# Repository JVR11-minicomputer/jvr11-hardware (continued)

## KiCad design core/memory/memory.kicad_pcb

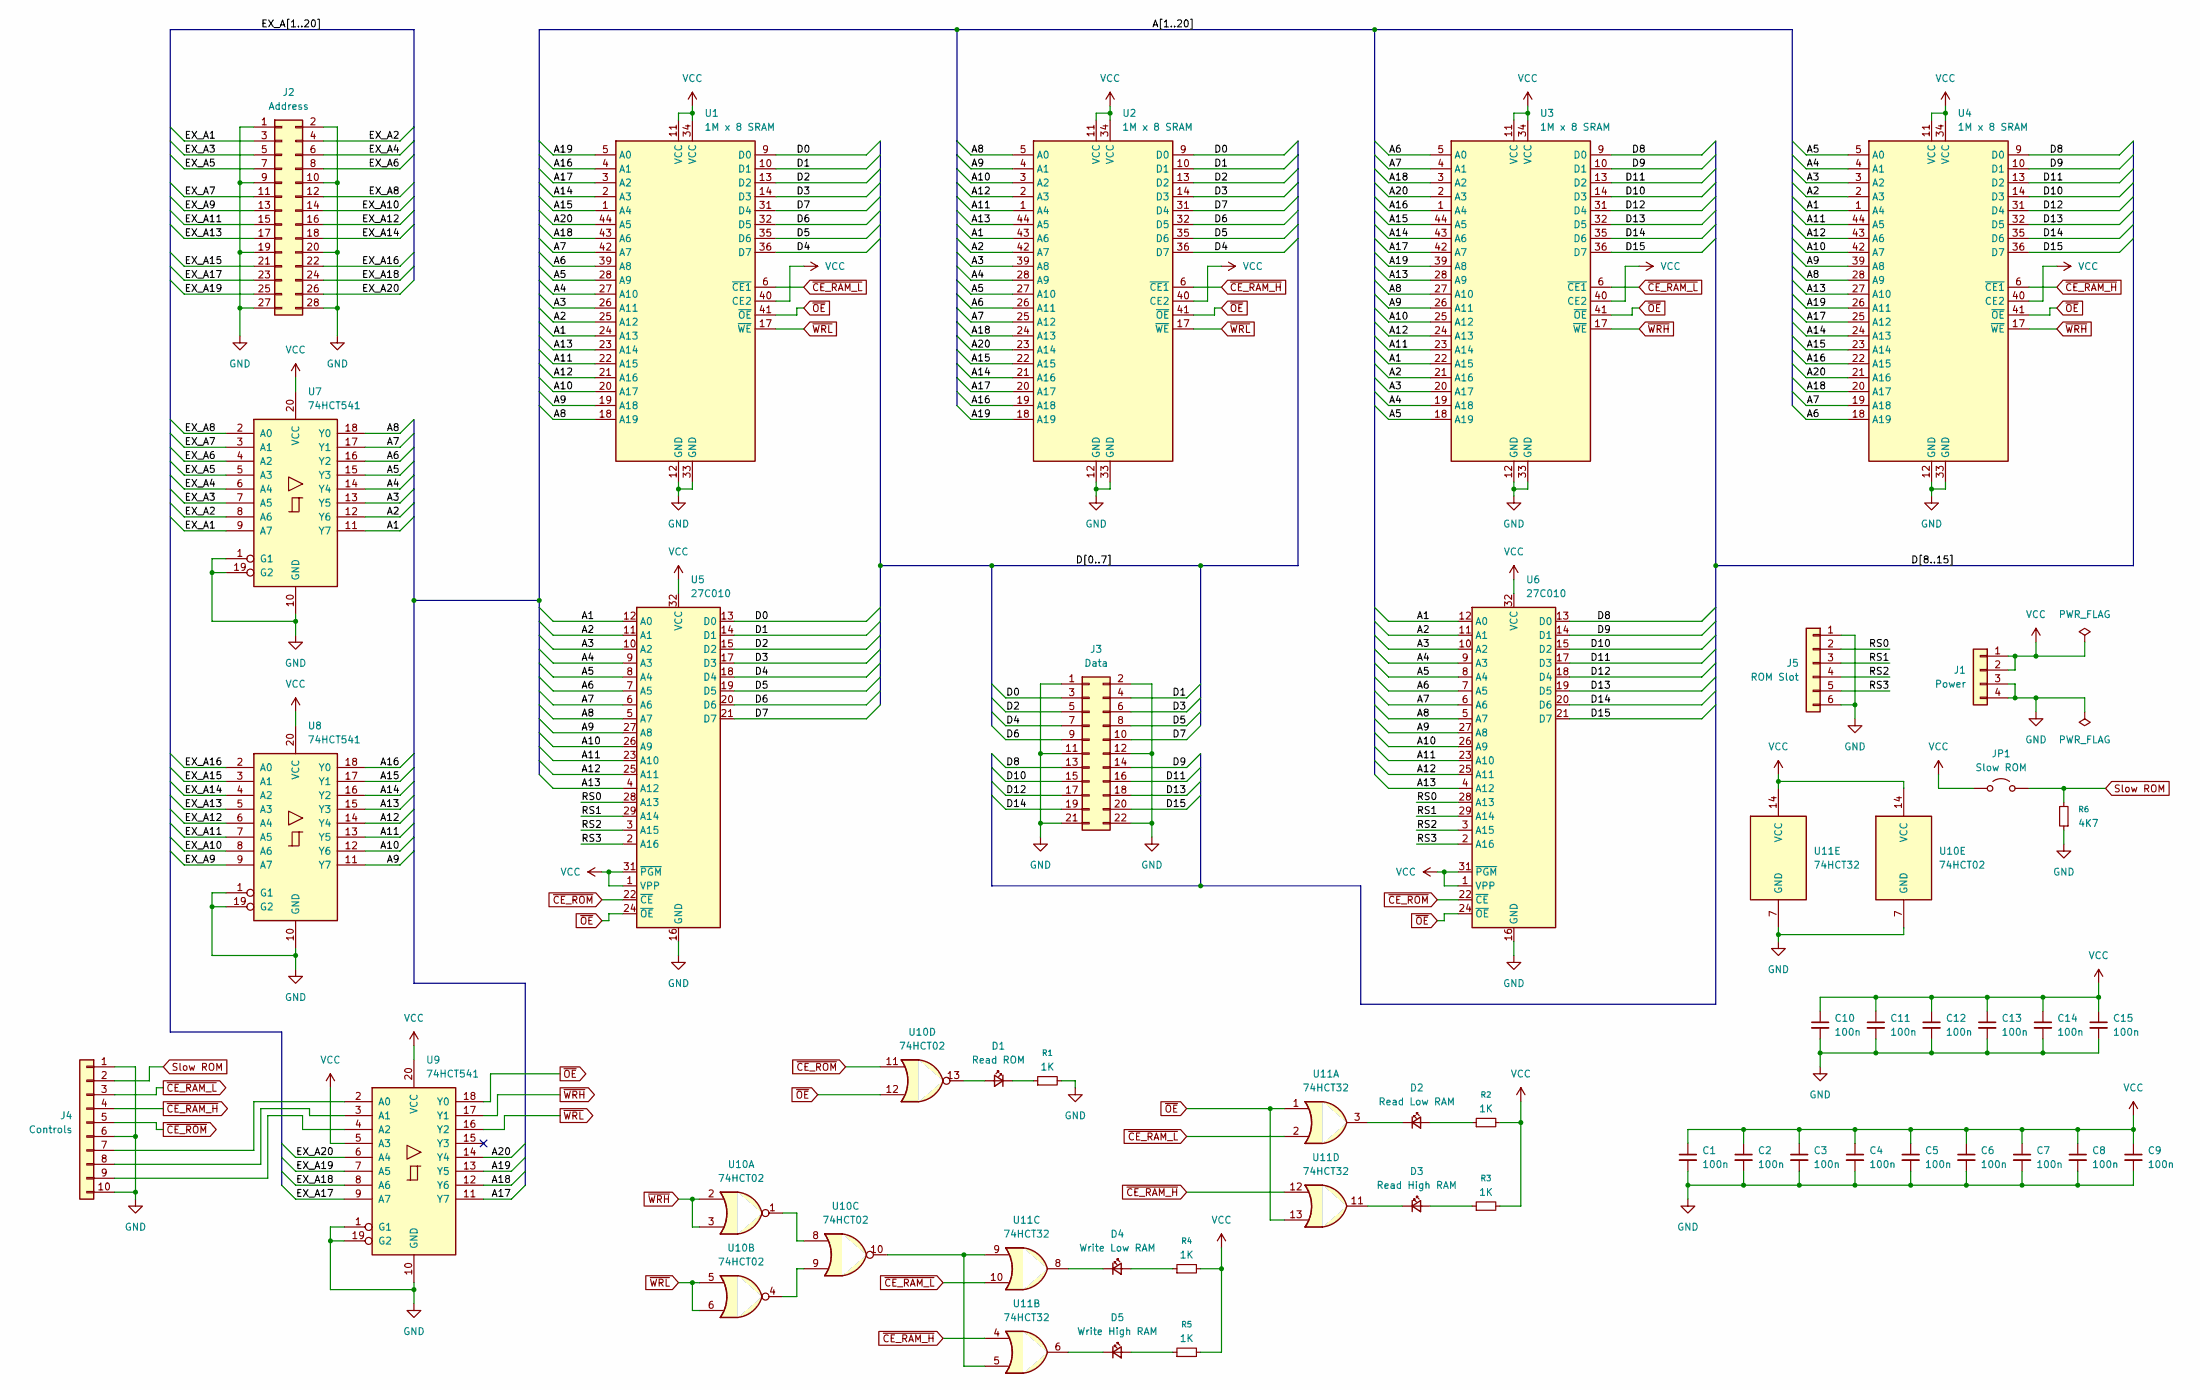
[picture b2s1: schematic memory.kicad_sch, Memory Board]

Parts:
C1, C2, C3, C4, C5, C6, C7, C8, C9, C10, C11, C12, C13, C14, C15: 100n; C_0805_2012Metric_Pad1.18x1.45mm_HandSolder
D1: Read ROM; LED_1206_3216Metric_Pad1.42x1.75mm_HandSolder
D2: Read Low RAM; LED_1206_3216Metric_Pad1.42x1.75mm_HandSolder
D3: Read High RAM; LED_1206_3216Metric_Pad1.42x1.75mm_HandSolder
D4: Write Low RAM; LED_1206_3216Metric_Pad1.42x1.75mm_HandSolder
D5: Write High RAM; LED_1206_3216Metric_Pad1.42x1.75mm_HandSolder
J1: Power; PinHeader_1x04_P2.54mm_Vertical
J2: Address; PinHeader_2x14_P2.54mm_Vertical
J3: Data; PinHeader_2x11_P2.54mm_Vertical
J4: Controls; PinHeader_1x10_P2.54mm_Vertical
J5: ROM Slot; PinHeader_1x06_P2.54mm_Vertical
JP1: Slow ROM; SolderJumper-2_P1.3mm_Open_Pad1.0x1.5mm
R1, R2, R3, R4, R5: 1K; R_0805_2012Metric_Pad1.20x1.40mm_HandSolder
R6: 4K7; R_0805_2012Metric_Pad1.20x1.40mm_HandSolder
U1, U2, U3, U4: 1M x 8 SRAM; TSOP-II-44_10.16x18.41mm_P0.8mm
U5, U6: 27C010; DIP-32_W15.24mm_Socket
U7, U8, U9: 74HCT541; SOIC-20W_7.5x12.8mm_P1.27mm
U10: 74HCT02; SOIC-14_3.9x8.7mm_P1.27mm
U11: 74HCT32; SOIC-14_3.9x8.7mm_P1.27mm

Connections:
/A1: U1.24 (A13), U2.43 (A6), U3.22 (A15), U4.1 (A4), U5.12 (A0), U6.12 (A0), U7.11 (Y7)
/A2: U1.25 (A12), U2.42 (A7), U3.21 (A16), U4.2 (A3), U5.11 (A1), U6.11 (A1), U7.12 (Y6)
/A3: U1.26 (A11), U2.39 (A8), U3.20 (A17), U4.3 (A2), U5.10 (A2), U6.10 (A2), U7.13 (Y5)
/A4: U1.27 (A10), U2.28 (A9), U3.19 (A18), U4.4 (A1), U5.9 (A3), U6.9 (A3), U7.14 (Y4)
/A5: U1.28 (A9), U2.27 (A10), U3.18 (A19), U4.5 (A0), U5.8 (A4), U6.8 (A4), U7.15 (Y3)
/A6: U1.39 (A8), U2.26 (A11), U3.5 (A0), U4.18 (A19), U5.7 (A5), U6.7 (A5), U7.16 (Y2)
/A7: U1.42 (A7), U2.25 (A12), U3.4 (A1), U4.19 (A18), U5.6 (A6), U6.6 (A6), U7.17 (Y1)
/A8: U1.18 (A19), U2.5 (A0), U3.27 (A10), U4.28 (A9), U5.5 (A7), U6.5 (A7), U7.18 (Y0)
/A9: U1.19 (A18), U2.4 (A1), U3.26 (A11), U4.39 (A8), U5.27 (A8), U6.27 (A8), U8.11 (Y7)
/A10: U1.20 (A17), U2.3 (A2), U3.25 (A12), U4.42 (A7), U5.26 (A9), U6.26 (A9), U8.12 (Y6)
/A11: U1.22 (A15), U2.1 (A4), U3.23 (A14), U4.44 (A5), U5.23 (A10), U6.23 (A10), U8.13 (Y5)
/A12: U1.21 (A16), U2.2 (A3), U3.24 (A13), U4.43 (A6), U5.25 (A11), U6.25 (A11), U8.14 (Y4)
/A13: U1.23 (A14), U2.44 (A5), U3.28 (A9), U4.27 (A10), U5.4 (A12), U6.4 (A12), U8.15 (Y3)
/A14: U1.2 (A3), U2.21 (A16), U3.43 (A6), U4.24 (A13), U8.16 (Y2)
/A15: U1.1 (A4), U2.22 (A15), U3.44 (A5), U4.23 (A14), U8.17 (Y1)
/A16: U1.4 (A1), U2.19 (A18), U3.1 (A4), U4.22 (A15), U8.18 (Y0)
/A17: U1.3 (A2), U2.20 (A17), U3.42 (A7), U4.25 (A12), U9.11 (Y7)
/A18: U1.43 (A6), U2.24 (A13), U3.3 (A2), U4.20 (A17), U9.12 (Y6)
/A19: U1.5 (A0), U2.18 (A19), U3.39 (A8), U4.26 (A11), U9.13 (Y5)
/A20: U1.44 (A5), U2.23 (A14), U3.2 (A3), U4.21 (A16), U9.14 (Y4)
/D0: J3.3, U1.9 (D0), U2.9 (D0), U5.13 (D0)
/D1: J3.4, U1.10 (D1), U2.10 (D1), U5.14 (D1)
/D2: J3.5, U1.13 (D2), U2.13 (D2), U5.15 (D2)
/D3: J3.6, U1.14 (D3), U2.14 (D3), U5.17 (D3)
/D4: J3.7, U1.36 (D7), U2.36 (D7), U5.18 (D4)
/D5: J3.8, U1.35 (D6), U2.35 (D6), U5.19 (D5)
/D6: J3.9, U1.32 (D5), U2.32 (D5), U5.20 (D6)
/D7: J3.10, U1.31 (D4), U2.31 (D4), U5.21 (D7)
/D8: J3.13, U3.9 (D0), U4.9 (D0), U6.13 (D0)
/D9: J3.14, U3.10 (D1), U4.10 (D1), U6.14 (D1)
/D10: J3.15, U3.14 (D3), U4.14 (D3), U6.15 (D2)
/D11: J3.16, U3.13 (D2), U4.13 (D2), U6.17 (D3)
/D12: J3.17, U3.31 (D4), U4.31 (D4), U6.18 (D4)
/D13: J3.18, U3.32 (D5), U4.32 (D5), U6.19 (D5)
/D14: J3.19, U3.35 (D6), U4.35 (D6), U6.20 (D6)
/D15: J3.20, U3.36 (D7), U4.36 (D7), U6.21 (D7)
/EX_A1: J2.3, U7.9 (A7)
/EX_A2: J2.4, U7.8 (A6)
/EX_A3: J2.5, U7.7 (A5)
/EX_A4: J2.6, U7.6 (A4)
/EX_A5: J2.7, U7.5 (A3)
/EX_A6: J2.8, U7.4 (A2)
/EX_A7: J2.11, U7.3 (A1)
/EX_A8: J2.12, U7.2 (A0)
/EX_A9: J2.13, U8.9 (A7)
/EX_A10: J2.14, U8.8 (A6)
/EX_A11: J2.15, U8.7 (A5)
/EX_A12: J2.16, U8.6 (A4)
/EX_A13: J2.17, U8.5 (A3)
/EX_A14: J2.18, U8.4 (A2)
/EX_A15: J2.21, U8.3 (A1)
/EX_A16: J2.22, U8.2 (A0)
/EX_A17: J2.23, U9.9 (A7)
/EX_A18: J2.24, U9.8 (A6)
/EX_A19: J2.25, U9.7 (A5)
/EX_A20: J2.26, U9.6 (A4)
/RS0: J5.2, U5.28 (A13), U6.28 (A13)
/RS1: J5.3, U5.29 (A14), U6.29 (A14)
/RS2: J5.4, U5.3 (A15), U6.3 (A15)
/RS3: J5.5, U5.2 (A16), U6.2 (A16)
GND: C1.2, C2.2, C3.2, C4.2, C5.2, C6.2, C7.2, C8.2, C9.2, C10.2, C11.2, C12.2, C13.2, C14.2, C15.2, J1.3, J1.4, J2.1, J2.2, J2.9, J2.10, J2.19, J2.20, J2.27, J2.28, J3.1, J3.2, J3.11, J3.12, J3.21, J3.22, J4.1, J4.6, J4.10, J5.1, J5.6, R1.2, R6.1, U1.12 (GND), U1.33 (GND), U2.12 (GND), U2.33 (GND), U3.12 (GND), U3.33 (GND), U4.12 (GND), U4.33 (GND), U5.16 (GND), U6.16 (GND), U7.1 (G1), U7.10 (GND), U7.19 (G2), U8.1 (G1), U8.10 (GND), U8.19 (G2), U9.1 (G1), U9.10 (GND), U9.19 (G2), U10.7 (GND), U11.7 (GND)
unnamed: D1.2 (A), U10.13
unnamed: D1.1 (K), R1.1
unnamed: D2.2 (A), R2.1
unnamed: D2.1 (K), U11.3
unnamed: D3.2 (A), R3.1
unnamed: D3.1 (K), U11.11
unnamed: D4.2 (A), R4.1
unnamed: D4.1 (K), U11.8
unnamed: D5.2 (A), R5.1
unnamed: D5.1 (K), U11.6
unnamed: J4.7, U9.2 (A0)
unnamed: J4.8, U9.3 (A1)
unnamed: J4.9, U9.4 (A2)
unnamed: U10.1, U10.8
unnamed: U10.4, U10.9
unnamed: U10.10, U11.5, U11.9
Slow ROM: J4.2, JP1.2 (B), R6.2
VCC: C1.1, C2.1, C3.1, C4.1, C5.1, C6.1, C7.1, C8.1, C9.1, C10.1, C11.1, C12.1, C13.1, C14.1, C15.1, J1.1, J1.2, JP1.1 (A), R2.2, R3.2, R4.2, R5.2, U1.11 (VCC), U1.34 (VCC), U1.40 (CE2), U2.11 (VCC), U2.34 (VCC), U2.40 (CE2), U3.11 (VCC), U3.34 (VCC), U3.40 (CE2), U4.11 (VCC), U4.34 (VCC), U4.40 (CE2), U5.1 (VPP), U5.31 (~PGM), U5.32 (VCC), U6.1 (VPP), U6.31 (~PGM), U6.32 (VCC), U7.20 (VCC), U8.20 (VCC), U9.5 (A3), U9.20 (VCC), U10.14 (VCC), U11.14 (VCC)
~CE_RAM_H: J4.4, U2.6 (~CE1), U4.6 (~CE1), U11.4, U11.12
~CE_RAM_L: J4.3, U1.6 (~CE1), U3.6 (~CE1), U11.2, U11.10
~CE_ROM: J4.5, U5.22 (~CE), U6.22 (~CE), U10.11
~OE: U1.41 (~OE), U2.41 (~OE), U3.41 (~OE), U4.41 (~OE), U5.24 (~OE), U6.24 (~OE), U9.18 (Y0), U10.12, U11.1, U11.13
~WRH: U3.17 (~WE), U4.17 (~WE), U9.17 (Y1), U10.2, U10.3
~WRL: U1.17 (~WE), U2.17 (~WE), U9.16 (Y2), U10.5, U10.6

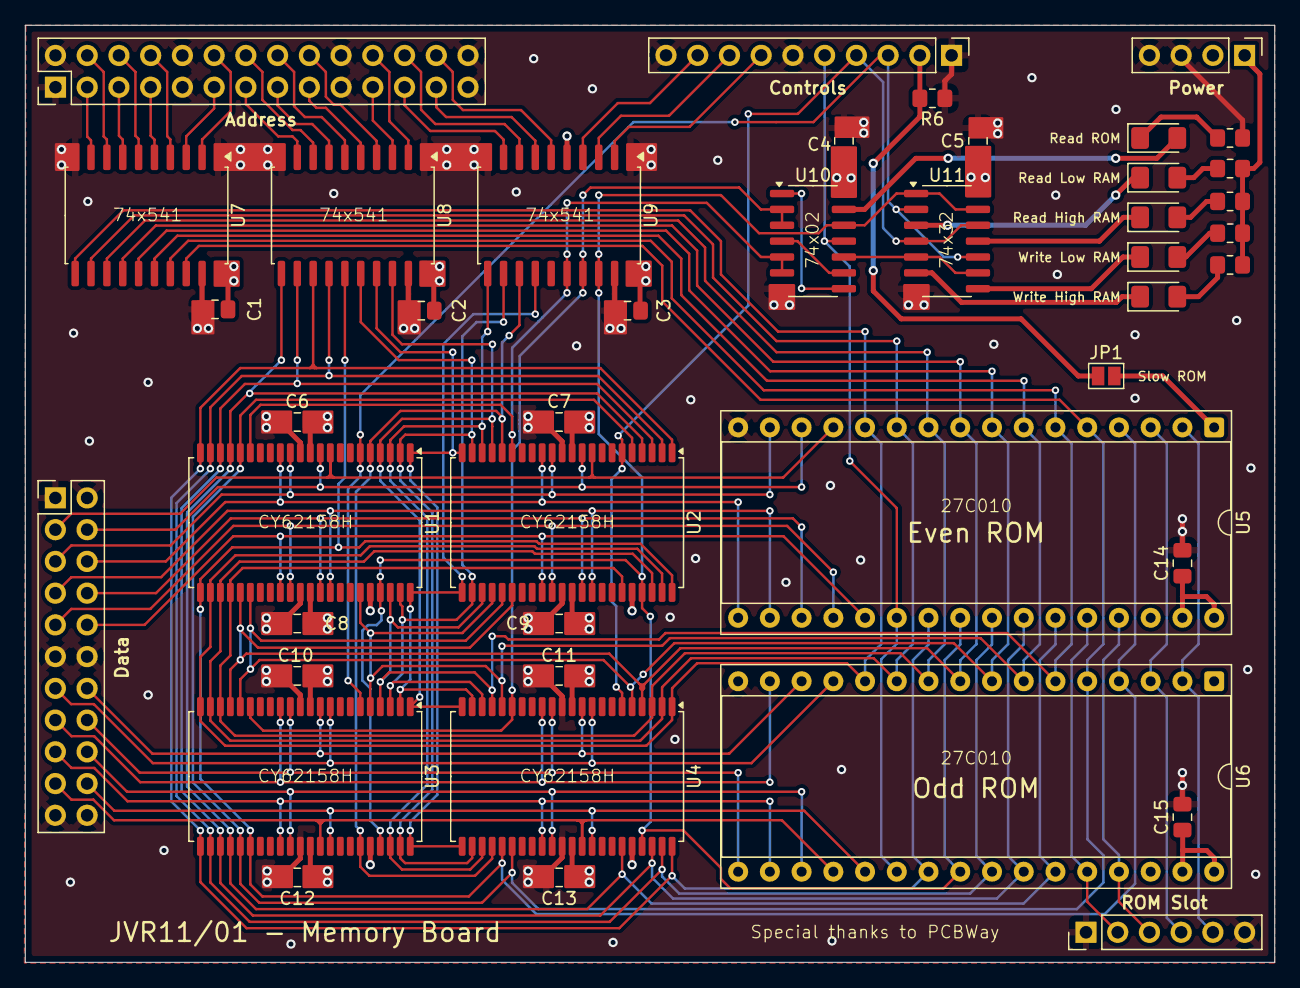
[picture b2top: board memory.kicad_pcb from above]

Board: 4 copper layers, 100.0 x 75.0 mm, 43 parts (0 on the bottom side), 85 nets.

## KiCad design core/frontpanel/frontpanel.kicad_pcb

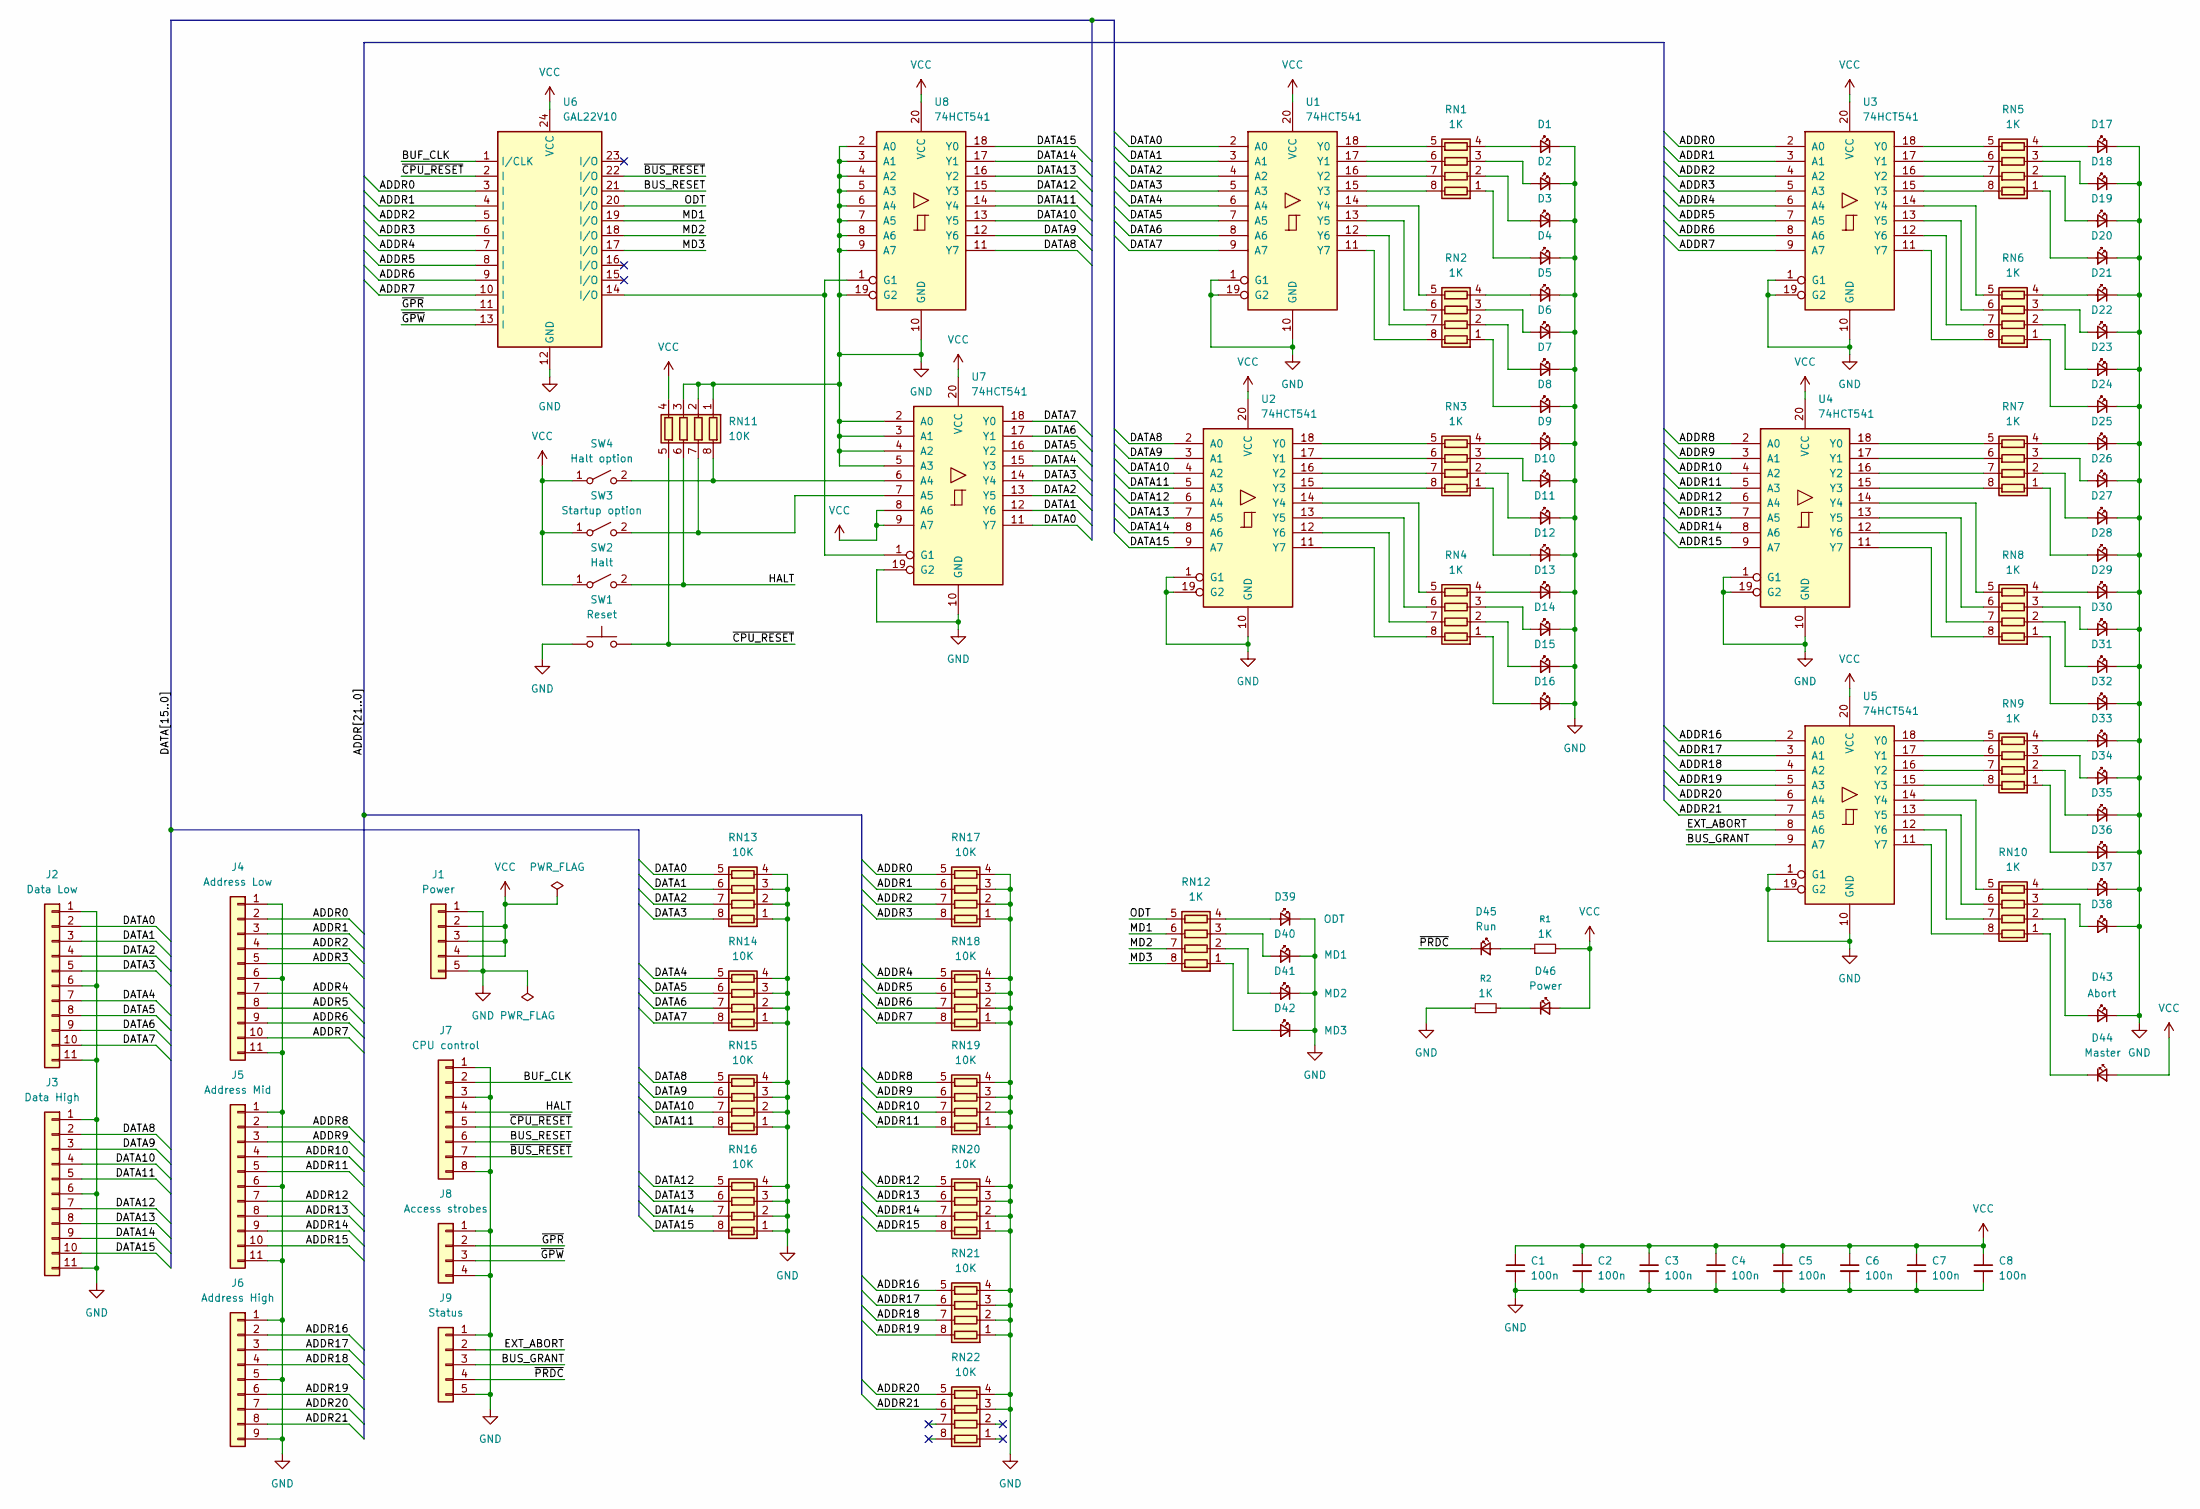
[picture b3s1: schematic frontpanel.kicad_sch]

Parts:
C1, C2, C3, C4, C5, C6, C7, C8: 100n; C_0805_2012Metric_Pad1.18x1.45mm_HandSolder
D1, D2, D3, D4, D5, D6, D7, D8, D9, D10, D11, D12, D13, D14, D15, D16, D17, D18, D19, D20, D21, D22, D23, D24, D25, D26, D27, D28, D29, D30, D31, D32, D33, D34, D35, D36, D37, D38: (amber); led_0805
D39: ODT; led_0805
D40: MD1; led_0805
D41: MD2; led_0805
D42: MD3; led_0805
D43: Abort; led_0805
D44: Master; led_0805
D45: Run; led_0805
D46: Power; led_0805
J1: Power; PinHeader_1x05_P2.54mm_Vertical
J2: Data Low; PinHeader_1x11_P2.54mm_Vertical
J3: Data High; PinHeader_1x11_P2.54mm_Vertical
J4: Address Low; PinHeader_1x11_P2.54mm_Vertical
J5: Address Mid; PinHeader_1x11_P2.54mm_Vertical
J6: Address High; PinHeader_1x09_P2.54mm_Vertical
J7: CPU control; PinHeader_1x08_P2.54mm_Vertical
J8: Access strobes; PinHeader_1x04_P2.54mm_Vertical
J9: Status; PinHeader_1x05_P2.54mm_Vertical
R1, R2: 1K; R_0805_2012Metric_Pad1.20x1.40mm_HandSolder
RN1, RN2, RN3, RN4, RN5, RN6, RN7, RN8, RN9, RN10, RN12: 1K; r_array_1206_x4
RN11, RN13, RN14, RN15, RN16, RN17, RN18, RN19, RN20, RN21, RN22: 10K; r_array_1206_x4
SW1: Reset; SW_TH_Tactile_Omron_B3F-100x
SW2: Halt; SW_DIP_SPSTx01_Slide_9.78x4.72mm_W7.62mm_P2.54mm
SW3: Startup option; SW_DIP_SPSTx01_Slide_9.78x4.72mm_W7.62mm_P2.54mm
SW4: Halt option; SW_DIP_SPSTx01_Slide_9.78x4.72mm_W7.62mm_P2.54mm
U1, U2, U3, U4, U5, U7, U8: 74HCT541; SOIC-20W_7.5x12.8mm_P1.27mm
U6: GAL22V10; DIP-24_W7.62mm_Socket

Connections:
/ADDR0: J4.2, RN17.5 (R4.2), U3.2 (A0), U6.3 (I)
/ADDR1: J4.3, RN17.6 (R3.2), U3.3 (A1), U6.4 (I)
/ADDR2: J4.4, RN17.7 (R2.2), U3.4 (A2), U6.5 (I)
/ADDR3: J4.5, RN17.8 (R1.2), U3.5 (A3), U6.6 (I)
/ADDR4: J4.7, RN18.5 (R4.2), U3.6 (A4), U6.7 (I)
/ADDR5: J4.8, RN18.6 (R3.2), U3.7 (A5), U6.8 (I)
/ADDR6: J4.9, RN18.7 (R2.2), U3.8 (A6), U6.9 (I)
/ADDR7: J4.10, RN18.8 (R1.2), U3.9 (A7), U6.10 (I)
/ADDR8: J5.2, RN19.5 (R4.2), U4.2 (A0)
/ADDR9: J5.3, RN19.6 (R3.2), U4.3 (A1)
/ADDR10: J5.4, RN19.7 (R2.2), U4.4 (A2)
/ADDR11: J5.5, RN19.8 (R1.2), U4.5 (A3)
/ADDR12: J5.7, RN20.5 (R4.2), U4.6 (A4)
/ADDR13: J5.8, RN20.6 (R3.2), U4.7 (A5)
/ADDR14: J5.9, RN20.7 (R2.2), U4.8 (A6)
/ADDR15: J5.10, RN20.8 (R1.2), U4.9 (A7)
/ADDR16: J6.2, RN21.5 (R4.2), U5.2 (A0)
/ADDR17: J6.3, RN21.6 (R3.2), U5.3 (A1)
/ADDR18: J6.4, RN21.7 (R2.2), U5.4 (A2)
/ADDR19: J6.6, RN21.8 (R1.2), U5.5 (A3)
/ADDR20: J6.7, RN22.5 (R4.2), U5.6 (A4)
/ADDR21: J6.8, RN22.6 (R3.2), U5.7 (A5)
/BUF_CLK: J7.2, U6.1 (I/CLK)
/BUS_GRANT: J9.3, U5.9 (A7)
/BUS_RESET: J7.6, U6.21 (I/O)
/DATA0: J2.2, RN13.5 (R4.2), U1.2 (A0), U7.11 (Y7)
/DATA1: J2.3, RN13.6 (R3.2), U1.3 (A1), U7.12 (Y6)
/DATA2: J2.4, RN13.7 (R2.2), U1.4 (A2), U7.13 (Y5)
/DATA3: J2.5, RN13.8 (R1.2), U1.5 (A3), U7.14 (Y4)
/DATA4: J2.7, RN14.5 (R4.2), U1.6 (A4), U7.15 (Y3)
/DATA5: J2.8, RN14.6 (R3.2), U1.7 (A5), U7.16 (Y2)
/DATA6: J2.9, RN14.7 (R2.2), U1.8 (A6), U7.17 (Y1)
/DATA7: J2.10, RN14.8 (R1.2), U1.9 (A7), U7.18 (Y0)
/DATA8: J3.2, RN15.5 (R4.2), U2.2 (A0), U8.11 (Y7)
/DATA9: J3.3, RN15.6 (R3.2), U2.3 (A1), U8.12 (Y6)
/DATA10: J3.4, RN15.7 (R2.2), U2.4 (A2), U8.13 (Y5)
/DATA11: J3.5, RN15.8 (R1.2), U2.5 (A3), U8.14 (Y4)
/DATA12: J3.7, RN16.5 (R4.2), U2.6 (A4), U8.15 (Y3)
/DATA13: J3.8, RN16.6 (R3.2), U2.7 (A5), U8.16 (Y2)
/DATA14: J3.9, RN16.7 (R2.2), U2.8 (A6), U8.17 (Y1)
/DATA15: J3.10, RN16.8 (R1.2), U2.9 (A7), U8.18 (Y0)
/EXT_ABORT: J9.2, U5.8 (A6)
/HALT: J7.4, RN11.6 (R3.2), SW2.2 (B)
/MD1: RN12.6 (R3.2), U6.19 (I/O)
/MD2: RN12.7 (R2.2), U6.18 (I/O)
/MD3: RN12.8 (R1.2), U6.17 (I/O)
/ODT: RN12.5 (R4.2), U6.20 (I/O)
/~BUS_RESET: J7.7, U6.22 (I/O)
/~CPU_RESET: J7.5, RN11.5 (R4.2), SW1.2, U6.2 (I)
/~GPR: J8.2, U6.11 (I)
/~GPW: J8.3, U6.13 (I)
/~PRDC: D45.1 (K), J9.4
GND: C1.2, C2.2, C3.2, C4.2, C5.2, C6.2, C7.2, C8.2, D1.1 (K), D2.1 (K), D3.1 (K), D4.1 (K), D5.1 (K), D6.1 (K), D7.1 (K), D8.1 (K), D9.1 (K), D10.1 (K), D11.1 (K), D12.1 (K), D13.1 (K), D14.1 (K), D15.1 (K), D16.1 (K), D17.1 (K), D18.1 (K), D19.1 (K), D20.1 (K), D21.1 (K), D22.1 (K), D23.1 (K), D24.1 (K), D25.1 (K), D26.1 (K), D27.1 (K), D28.1 (K), D29.1 (K), D30.1 (K), D31.1 (K), D32.1 (K), D33.1 (K), D34.1 (K), D35.1 (K), D36.1 (K), D37.1 (K), D38.1 (K), D39.1 (K), D40.1 (K), D41.1 (K), D42.1 (K), D43.1 (K), J1.1, J1.5, J2.1, J2.6, J2.11, J3.1, J3.6, J3.11, J4.1, J4.6, J4.11, J5.1, J5.6, J5.11, J6.1, J6.5, J6.9, J7.1, J7.3, J7.8, J8.1, J8.4, J9.1, J9.5, R2.1, RN11.1 (R1.1), RN11.2 (R2.1), RN11.3 (R3.1), RN13.1 (R1.1), RN13.2 (R2.1), RN13.3 (R3.1), RN13.4 (R4.1), RN14.1 (R1.1), RN14.2 (R2.1), RN14.3 (R3.1), RN14.4 (R4.1), RN15.1 (R1.1), RN15.2 (R2.1), RN15.3 (R3.1), RN15.4 (R4.1), RN16.1 (R1.1), RN16.2 (R2.1), RN16.3 (R3.1), RN16.4 (R4.1), RN17.1 (R1.1), RN17.2 (R2.1), RN17.3 (R3.1), RN17.4 (R4.1), RN18.1 (R1.1), RN18.2 (R2.1), RN18.3 (R3.1), RN18.4 (R4.1), RN19.1 (R1.1), RN19.2 (R2.1), RN19.3 (R3.1), RN19.4 (R4.1), RN20.1 (R1.1), RN20.2 (R2.1), RN20.3 (R3.1), RN20.4 (R4.1), RN21.1 (R1.1), RN21.2 (R2.1), RN21.3 (R3.1), RN21.4 (R4.1), RN22.3 (R3.1), RN22.4 (R4.1), SW1.1, U1.1 (G1), U1.10 (GND), U1.19 (G2), U2.1 (G1), U2.10 (GND), U2.19 (G2), U3.1 (G1), U3.10 (GND), U3.19 (G2), U4.1 (G1), U4.10 (GND), U4.19 (G2), U5.1 (G1), U5.10 (GND), U5.19 (G2), U6.12 (GND), U7.2 (A0), U7.3 (A1), U7.4 (A2), U7.5 (A3), U7.10 (GND), U7.19 (G2), U8.2 (A0), U8.3 (A1), U8.4 (A2), U8.5 (A3), U8.6 (A4), U8.7 (A5), U8.8 (A6), U8.9 (A7), U8.10 (GND), U8.19 (G2)
unnamed: D1.2 (A), RN1.4 (R4.1)
unnamed: D2.2 (A), RN1.3 (R3.1)
unnamed: D3.2 (A), RN1.2 (R2.1)
unnamed: D4.2 (A), RN1.1 (R1.1)
unnamed: D5.2 (A), RN2.4 (R4.1)
unnamed: D6.2 (A), RN2.3 (R3.1)
unnamed: D7.2 (A), RN2.2 (R2.1)
unnamed: D8.2 (A), RN2.1 (R1.1)
unnamed: D9.2 (A), RN3.4 (R4.1)
unnamed: D10.2 (A), RN3.3 (R3.1)
unnamed: D11.2 (A), RN3.2 (R2.1)
unnamed: D12.2 (A), RN3.1 (R1.1)
unnamed: D13.2 (A), RN4.4 (R4.1)
unnamed: D14.2 (A), RN4.3 (R3.1)
unnamed: D15.2 (A), RN4.2 (R2.1)
unnamed: D16.2 (A), RN4.1 (R1.1)
unnamed: D17.2 (A), RN5.4 (R4.1)
unnamed: D18.2 (A), RN5.3 (R3.1)
unnamed: D19.2 (A), RN5.2 (R2.1)
unnamed: D20.2 (A), RN5.1 (R1.1)
unnamed: D21.2 (A), RN6.4 (R4.1)
unnamed: D22.2 (A), RN6.3 (R3.1)
unnamed: D23.2 (A), RN6.2 (R2.1)
unnamed: D24.2 (A), RN6.1 (R1.1)
unnamed: D25.2 (A), RN7.4 (R4.1)
unnamed: D26.2 (A), RN7.3 (R3.1)
unnamed: D27.2 (A), RN7.2 (R2.1)
unnamed: D28.2 (A), RN7.1 (R1.1)
unnamed: D29.2 (A), RN8.4 (R4.1)
unnamed: D30.2 (A), RN8.3 (R3.1)
unnamed: D31.2 (A), RN8.2 (R2.1)
unnamed: D32.2 (A), RN8.1 (R1.1)
unnamed: D33.2 (A), RN9.4 (R4.1)
unnamed: D34.2 (A), RN9.3 (R3.1)
unnamed: D35.2 (A), RN9.2 (R2.1)
unnamed: D36.2 (A), RN9.1 (R1.1)
unnamed: D37.2 (A), RN10.4 (R4.1)
unnamed: D38.2 (A), RN10.3 (R3.1)
unnamed: D39.2 (A), RN12.4 (R4.1)
unnamed: D40.2 (A), RN12.3 (R3.1)
unnamed: D41.2 (A), RN12.2 (R2.1)
unnamed: D42.2 (A), RN12.1 (R1.1)
unnamed: D43.2 (A), RN10.2 (R2.1)
unnamed: D44.1 (K), RN10.1 (R1.1)
unnamed: D45.2 (A), R1.1
unnamed: D46.1 (K), R2.2
unnamed: RN1.8 (R1.2), U1.15 (Y3)
unnamed: RN1.7 (R2.2), U1.16 (Y2)
unnamed: RN1.6 (R3.2), U1.17 (Y1)
unnamed: RN1.5 (R4.2), U1.18 (Y0)
unnamed: RN2.8 (R1.2), U1.11 (Y7)
unnamed: RN2.7 (R2.2), U1.12 (Y6)
unnamed: RN2.6 (R3.2), U1.13 (Y5)
unnamed: RN2.5 (R4.2), U1.14 (Y4)
unnamed: RN3.8 (R1.2), U2.15 (Y3)
unnamed: RN3.7 (R2.2), U2.16 (Y2)
unnamed: RN3.6 (R3.2), U2.17 (Y1)
unnamed: RN3.5 (R4.2), U2.18 (Y0)
unnamed: RN4.8 (R1.2), U2.11 (Y7)
unnamed: RN4.7 (R2.2), U2.12 (Y6)
unnamed: RN4.6 (R3.2), U2.13 (Y5)
unnamed: RN4.5 (R4.2), U2.14 (Y4)
unnamed: RN5.8 (R1.2), U3.15 (Y3)
unnamed: RN5.7 (R2.2), U3.16 (Y2)
unnamed: RN5.6 (R3.2), U3.17 (Y1)
unnamed: RN5.5 (R4.2), U3.18 (Y0)
unnamed: RN6.8 (R1.2), U3.11 (Y7)
unnamed: RN6.7 (R2.2), U3.12 (Y6)
unnamed: RN6.6 (R3.2), U3.13 (Y5)
unnamed: RN6.5 (R4.2), U3.14 (Y4)
unnamed: RN7.8 (R1.2), U4.15 (Y3)
unnamed: RN7.7 (R2.2), U4.16 (Y2)
unnamed: RN7.6 (R3.2), U4.17 (Y1)
unnamed: RN7.5 (R4.2), U4.18 (Y0)
unnamed: RN8.8 (R1.2), U4.11 (Y7)
unnamed: RN8.7 (R2.2), U4.12 (Y6)
unnamed: RN8.6 (R3.2), U4.13 (Y5)
unnamed: RN8.5 (R4.2), U4.14 (Y4)
unnamed: RN9.8 (R1.2), U5.15 (Y3)
unnamed: RN9.7 (R2.2), U5.16 (Y2)
unnamed: RN9.6 (R3.2), U5.17 (Y1)
unnamed: RN9.5 (R4.2), U5.18 (Y0)
unnamed: RN10.8 (R1.2), U5.11 (Y7)
unnamed: RN10.7 (R2.2), U5.12 (Y6)
unnamed: RN10.6 (R3.2), U5.13 (Y5)
unnamed: RN10.5 (R4.2), U5.14 (Y4)
unnamed: RN11.8 (R1.2), SW4.2 (B), U7.6 (A4)
unnamed: RN11.7 (R2.2), SW3.2 (B), U7.7 (A5)
unnamed: U6.14 (I/O), U7.1 (G1), U8.1 (G1)
VCC: C1.1, C2.1, C3.1, C4.1, C5.1, C6.1, C7.1, C8.1, D44.2 (A), D46.2 (A), J1.2, J1.3, J1.4, R1.2, RN11.4 (R4.1), SW2.1 (A), SW3.1 (A), SW4.1 (A), U1.20 (VCC), U2.20 (VCC), U3.20 (VCC), U4.20 (VCC), U5.20 (VCC), U6.24 (VCC), U7.8 (A6), U7.9 (A7), U7.20 (VCC), U8.20 (VCC)

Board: 2 copper layers, 99 parts (9 on the bottom side), 143 nets, no tracks yet.

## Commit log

2025-09-01 Schematics and PLD sources for phase 1
2025-09-05 Added license
2025-09-08 Added an image of the computer
2025-09-08 Update: UART's reset problem fixed
2025-09-09 KiCad component library for custom chips
2025-09-09 Added 3D model of DCJ11
2025-09-09 Added symbol for EPM7064SLC44 and worksheet template
2025-09-11 Schematics for CPU board
2025-09-14 Fix: no need to expose CPU's abort signal to frontpanel
2025-09-14 Added footprint for 4x 1206 resistor array
2025-09-14 Added schematics of the frontpanel
2026-03-01 Update: March 2026
2026-03-25 memory PCB & PCBWay sponsorship
2026-05-20 Update May 2026 & IO Bridge WIP
2026-05-20 Update May 2026
